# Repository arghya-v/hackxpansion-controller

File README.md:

# hackxpansion module 1: SD Card Reader and Volume Control

**Crates: pkg:cargo/SD_card_driver@0.1.1**

A custom SD card module with three buttons for music storage and controls, using Xpanse API for hardware/module integration.

# Images

### Firmware

The firmware is responsible for communicating with the hardware.

The SD card is connected through SPI.

The current hardware mapping uses:

| GPIO  | Function   |
| ----- | ---------- |
| GPIO2 | SPI SCK    |
| GPIO3 | SPI MISO   |
| GPIO4 | SPI MOSI   |
| GPIO5 | Button A   |
| GPIO6 | Button B   |
| GPIO7 | Button X   |
| GPIO9 | SD card CS |

See the [Xpanse API docs](https://docs.rs/xpanse-api/latest/xpanse_api/index.html)

---

## SD Card Filesystem

Its purpose is to abstract away the lower-level SD card communication so the application can work with files rather than dealing directly with SPI commands.

The filesystem layer provides functionality for:

* Opening the SD card
* Opening the first volume
* Opening the root directory
* Reading files
* Writing files
* Listing files in the root directory
* Closing directories and volumes

This is what the stack looks like:

```text
SD Card
   │
   ▼
  SPI
   │
   ▼
Xpanse SpiBusHandle
   │
   ▼
embedded-sdmmc
   │
   ▼
Filesystem
   │
   ▼
Application
```

This means the application itself does not need to know how the SD card communicates over SPI.

---

This was all possible thanks to [Hackspansion: A hackclub YSWS](http://hackxpansion.hackclub.com/)

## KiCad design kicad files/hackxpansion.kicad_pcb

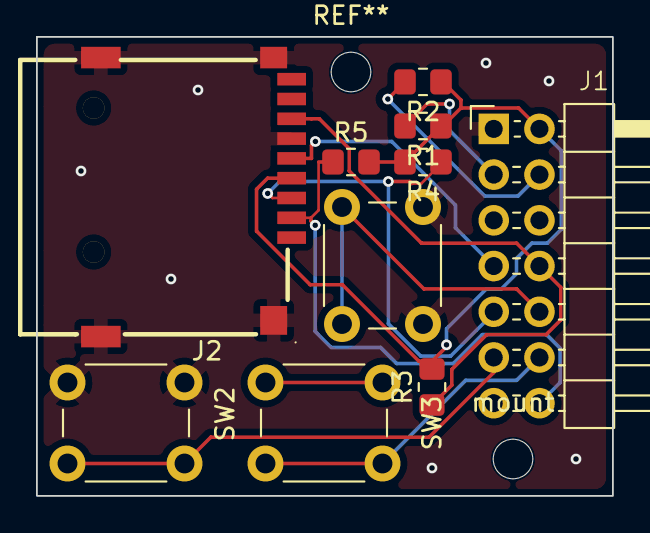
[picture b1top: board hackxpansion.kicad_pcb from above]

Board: 2 copper layers, 32.0 x 25.5 mm, 11 parts (0 on the bottom side), 11 nets.

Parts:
J1: Male_Module
J2: Micro_SD_Card_Det1; C381082_TF-SMD_XKTF-015-N
R1: 1k; R_0805_2012Metric_Pad1.20x1.40mm_HandSolder
R2: 30k; R_0805_2012Metric_Pad1.20x1.40mm_HandSolder
R3, R4, R5: 10k; R_0805_2012Metric_Pad1.20x1.40mm_HandSolder
SW1, SW2, SW3: SW_Push; SW_PUSH_6mm
mount: MountingHole_2.2mm_M2

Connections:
+3V3: J1.2 (3V3), J2.4 (VDD), R1.1, R2.1, R3.2, R4.2, R5.2
/BTN1: J1.10 (GPIO5), SW1.1
/BTN2: J1.11 (GPIO6), SW2.1
/BTN3: J1.12 (GPIO7), SW3.1 (1_1)
/P2: J1.7 (GPI02), J2.5 (CLK)
/P3: J1.8 (GPIO3), J2.7 (DAT0), R3.1
/P4: J1.9 (GPIO4), J2.3 (CMD), R4.1
/P9: J1.14 (GPIO9), J2.2 (DAT3/CD), R5.1
GND: J1.1 (GND), J2.6 (VSS), J2.10 (GND), J2.11 (GND), J2.12 (GND), J2.13 (GND), SW1.2, SW2.2
unnamed: J1.3 (MD0), R1.2
unnamed: J1.4 (MD1), R2.2

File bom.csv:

Designator,Footprint,Quantity,Value,LCSC Part #
J1,Male_Module,1,~,
J2,C381082_TF-SMD_XKTF-015-N,1,Micro_SD_Card_Det1,C381082
R1,0805,1,1k,
R2,0805,1,30k,
"R3, R4, R5",0805,3,10k,
"SW1, SW2, SW3",SW_PUSH_6mm,3,SW_Push,

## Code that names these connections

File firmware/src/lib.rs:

#![no_std]
pub mod filesystem;

use embassy_rp::{
    bind_interrupts,
    gpio::{Level, Output},
    peripherals::{DMA_CH0, DMA_CH1},
    spi::{self},
};

use xpanse_api::{
    bus::{
        allocator::BusAllocator,
        spi::SpiBusHandle,
    },
    driver::{Driver, DriverError, DriverMeta},
    gpio_bank::{BankPins, GpioBank},
    interfaces::buttons::{pin_button, A, B, X},
    metadata::{ModuleDetectResistor, ModuleID, ModuleSlot},
    registry::Registry,
};

// Both DMA_CH0 and DMA_CH1 use DMA_IRQ_0 on the RP235x.
bind_interrupts!(pub struct Irqs {
    DMA_IRQ_0 =>
        embassy_rp::dma::InterruptHandler<DMA_CH0>,
        embassy_rp::dma::InterruptHandler<DMA_CH1>;
});

pub struct SdCard {
    pub spi: SpiBusHandle,
    pub cs: Output<'static>,
}

pub struct SdCardDriver;

impl DriverMeta for SdCardDriver {
    const ID: ModuleID = ModuleID {
        md0: ModuleDetectResistor::R1K,
        md1: ModuleDetectResistor::R30K,
    };
}

impl<G> Driver<G> for SdCardDriver
where
    G: BankPins,
{
    async fn create(
        gpio_bank: GpioBank<G>,
        slot: ModuleSlot,
        registry: &mut Registry,
        bus_allocator: &mut BusAllocator,
    ) -> Result<(), DriverError> {

        // -------------------------
        // Buttons
        // -------------------------

        registry.register(
            slot,
            Self::ID,
            pin_button::<A>(gpio_bank.gpio5.into()),
        );

        registry.register(
            slot,
            Self::ID,
            pin_button::<B>(gpio_bank.gpio6.into()),
        );

        registry.register(
            slot,
            Self::ID,
            pin_button::<X>(gpio_bank.gpio7.into()),
        );

        // -------------------------
        // SPI
        //
        // GPIO2 = SCK
        // GPIO3 = MISO
        // GPIO4 = MOSI
        // GPIO9 = CS
        // -------------------------

        let spi = bus_allocator
            .create_spi_hardware::<G::SPI, DMA_CH0, DMA_CH1, _>(
                gpio_bank.gpio2, // SCK
                gpio_bank.gpio4, // MOSI
                gpio_bank.gpio3, // MISO
                Irqs,
                spi::Config::default(),
            )
            .map_err(|_| DriverError::InitFailed)?;

        // SD card chip select.
        //
        // SD cards are selected when CS is LOW, so we start
        // deselected with CS HIGH.
        let cs = Output::new(
            gpio_bank.gpio9,
            Level::High,
        );

        // -------------------------
        // Register SD card resource
        // -------------------------

        registry.register(
            slot,
            Self::ID,
            SdCard {
                spi,
                cs,
            },
        );

        Ok(())
    }
}
